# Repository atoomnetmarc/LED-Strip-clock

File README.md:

# Status

This project is in the idea stage.

Next step would be to test if the new schematic could work before ordering the first PCB.

# Why?

I made a huge LED clock with pieces of LED strip in 2013 using an [ATmega328 and DS3231 RTC](ATmega328%20version/). It has been running great and keeping time just fine. Lets break it by upgrading it.

This project will upgrade the ~~spagetti~~ old circuit to an internet connected LED strip clock neatly on a PCB. The brains will be a Wemos D1 mini and will use NTP to synchronize the time.

# Schematic

The [circuit](Kicad/LED%20Strip%20clock.pdf) recycles the same TPIC6B595 power shift registers and changes the ATmega328 for a ESP8266 and the DS3231 for a DS3231MZ. A 74HCT244 buffer translates between the 3.3V outputs of the ESP8266 and the 5V inputs of the shift register. The original circuit has a rotary encoder to set the light intensity and the current time. The new circuit will only use the rotary encoder to set the light intensity.

Render:

Real:

My [Kicad library](https://github.com/atoomnetmarc/ATOOMNETKICAD) is used in this project.

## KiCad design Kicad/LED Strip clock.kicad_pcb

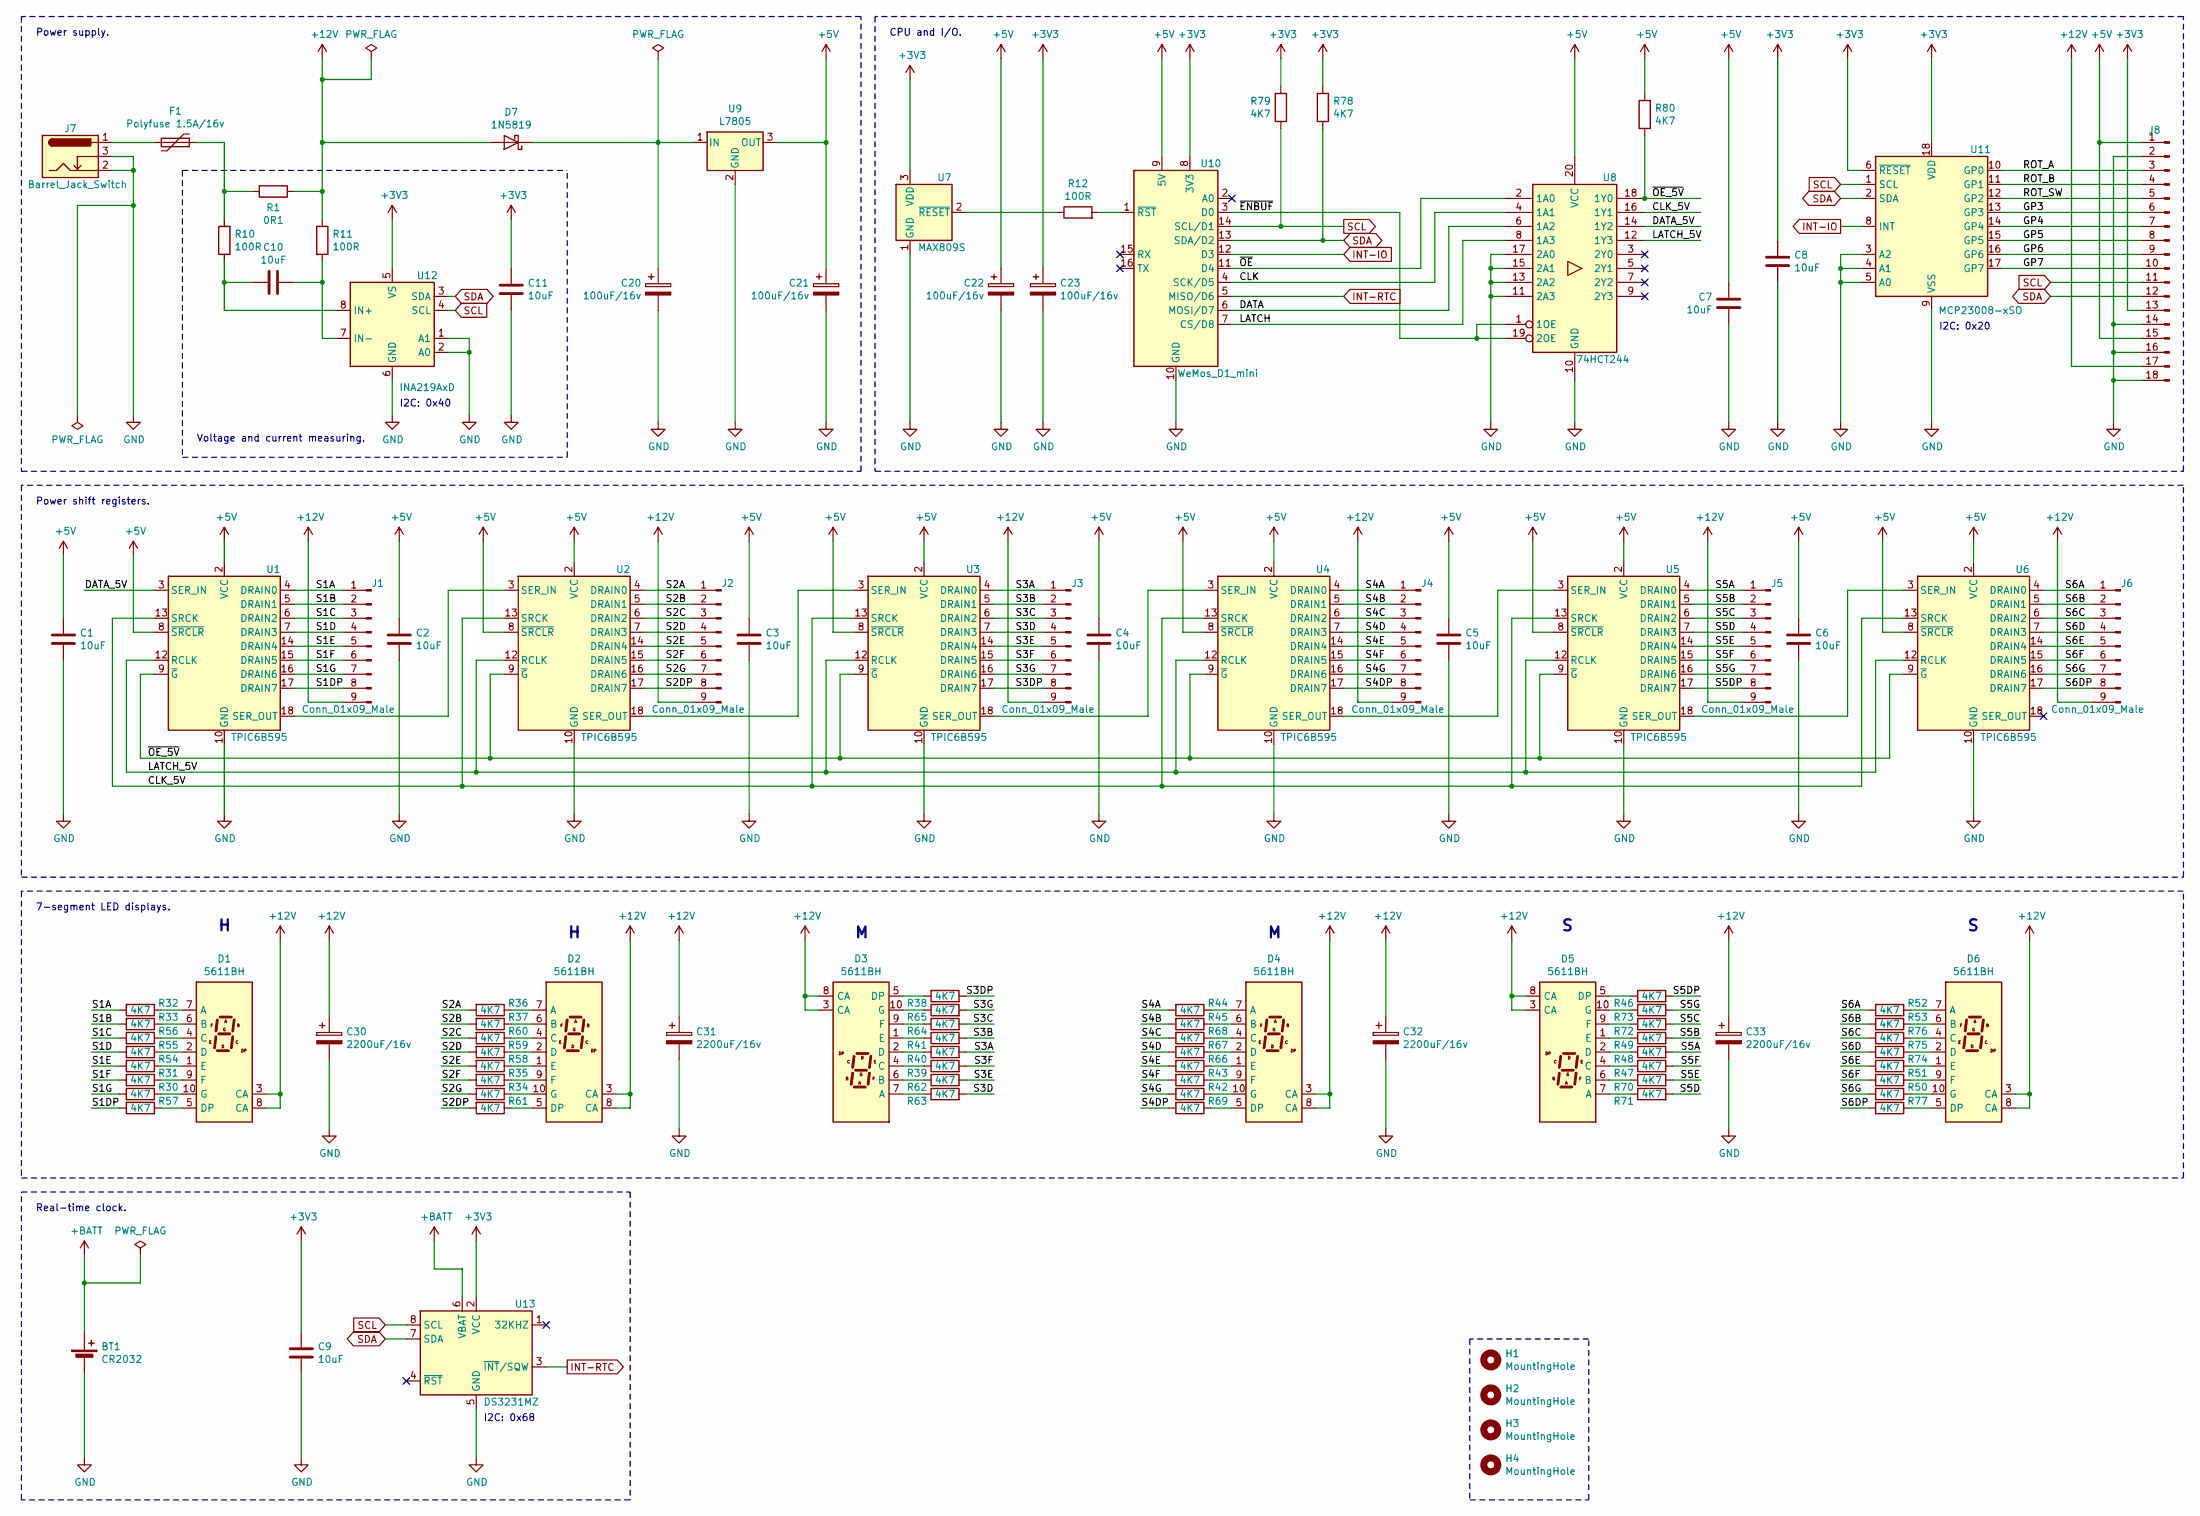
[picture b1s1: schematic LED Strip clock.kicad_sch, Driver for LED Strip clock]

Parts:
BT1: CR2032; BatteryHolder-cr2032
C1, C2, C3, C4, C5, C6, C7, C8, C9, C10, C11: 10uF; C_0805_2012Metric_Pad1.18x1.45mm_HandSolder
C20, C21, C22, C23: 100uF/16v; CP_Radial_D5.0mm_P2.00mm
C30, C31, C32, C33: 2200uF/16v; CP_Radial_D10.0mm_P5.00mm
D1, D2, D3, D4, D5, D6: 5611BH
D7: 1N5819; D_DO-41_SOD81_P10.16mm_Horizontal
F1: Polyfuse 1.5A/16v; Fuse_Bourns_MF-RG1000
H1, H2, H3, H4: MountingHole; MountingHole_3.2mm_M3
J1, J2, J3, J4, J5, J6: Conn_01x09_Male; PinHeader_1x09_P2.54mm_Vertical
J7: Barrel_Jack_Switch; BarrelJack_Horizontal
J8: Conn_01x18_Male; PinHeader_1x18_P2.54mm_Vertical
R1: 0R1; R_2512_6332Metric_Pad1.52x3.35mm_HandSolder
R10, R11, R12: 100R; R_0805_2012Metric_Pad1.20x1.40mm_HandSolder
R30, R31, R32, R33, R34, R35, R36, R37, R38, R39, R40, R41, R42, R43, R44, R45, R46, R47, R48, R49, R50, R51, R52, R53, R54, R55, R56, R57, R58, R59, R60, R61, R62, R63, R64, R65, R66, R67, R68, R69, R70, R71, R72, R73, R74, R75, R76, R77, R78, R79, R80: 4K7; R_0805_2012Metric_Pad1.20x1.40mm_HandSolder
U1, U2, U3, U4, U5, U6: TPIC6B595; DIP-20_W7.62mm_LongPads
U7: MAX809S; SOT-23
U8: 74HCT244; DIP-20_W7.62mm_LongPads
U9: L7805; TO-263-2
U10: WeMos_D1_mini; WEMOS_D1_mini_light
U11: MCP23008-xSO; SOIC-18W_7.5x11.6mm_P1.27mm
U12: INA219AxD; SOIC-8_3.9x4.9mm_P1.27mm
U13: DS3231MZ; SOIC-8_3.9x4.9mm_P1.27mm

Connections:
+3V3: C8.1, C9.1, C11.1, C23.1, J8.13, R78.2, R79.2, U7.3 (VDD), U10.8 (3V3), U11.6 (~RESET), U11.18 (VDD), U12.5 (VS), U13.2 (VCC)
+5V: C1.1, C2.1, C3.1, C4.1, C5.1, C6.1, C7.1, C21.1, C22.1, J8.1, J8.15, R80.2, U1.2 (VCC), U1.8 (~SRCLR), U2.2 (VCC), U2.8 (~SRCLR), U3.2 (VCC), U3.8 (~SRCLR), U4.2 (VCC), U4.8 (~SRCLR), U5.2 (VCC), U5.8 (~SRCLR), U6.2 (VCC), U6.8 (~SRCLR), U8.20 (VCC), U9.3 (OUT), U10.9 (5V)
+12V: C30.1, C31.1, C32.1, C33.1, D1.3 (CA), D1.8 (CA), D2.3 (CA), D2.8 (CA), D3.3 (CA), D3.8 (CA), D4.3 (CA), D4.8 (CA), D5.3 (CA), D5.8 (CA), D6.3 (CA), D6.8 (CA), D7.2 (A), J1.9, J2.9, J3.9, J4.9, J5.9, J6.9, J8.17, R1.1, R11.1
+BATT: BT1.1 (+), U13.6 (VBAT)
/CLK: U8.4 (1A1), U10.4 (SCK/D5)
/CLK_5V: U1.13 (SRCK), U2.13 (SRCK), U3.13 (SRCK), U4.13 (SRCK), U5.13 (SRCK), U6.13 (SRCK), U8.16 (1Y1)
/DATA: U8.6 (1A2), U10.6 (MOSI/D7)
/DATA_5V: U1.3 (SER_IN), U8.14 (1Y2)
/GP3: J8.6, U11.13 (GP3)
/GP4: J8.7, U11.14 (GP4)
/GP5: J8.8, U11.15 (GP5)
/GP6: J8.9, U11.16 (GP6)
/GP7: J8.10, U11.17 (GP7)
/LATCH: U8.8 (1A3), U10.7 (CS/D8)
/LATCH_5V: U1.12 (RCLK), U2.12 (RCLK), U3.12 (RCLK), U4.12 (RCLK), U5.12 (RCLK), U6.12 (RCLK), U8.12 (1Y3)
/ROT_A: J8.3, U11.10 (GP0)
/ROT_B: J8.4, U11.11 (GP1)
/ROT_SW: J8.5, U11.12 (GP2)
/S1A: J1.1, R32.2, U1.4 (DRAIN0)
/S1B: J1.2, R33.2, U1.5 (DRAIN1)
/S1C: J1.3, R56.2, U1.6 (DRAIN2)
/S1D: J1.4, R55.2, U1.7 (DRAIN3)
/S1DP: J1.8, R57.2, U1.17 (DRAIN7)
/S1E: J1.5, R54.2, U1.14 (DRAIN4)
/S1F: J1.6, R31.2, U1.15 (DRAIN5)
/S1G: J1.7, R30.2, U1.16 (DRAIN6)
/S2A: J2.1, R36.2, U2.4 (DRAIN0)
/S2B: J2.2, R37.2, U2.5 (DRAIN1)
/S2C: J2.3, R60.2, U2.6 (DRAIN2)
/S2D: J2.4, R59.2, U2.7 (DRAIN3)
/S2DP: J2.8, R61.2, U2.17 (DRAIN7)
/S2E: J2.5, R58.2, U2.14 (DRAIN4)
/S2F: J2.6, R35.2, U2.15 (DRAIN5)
/S2G: J2.7, R34.2, U2.16 (DRAIN6)
/S3A: J3.1, R40.2, U3.4 (DRAIN0)
/S3B: J3.2, R41.2, U3.5 (DRAIN1)
/S3C: J3.3, R64.2, U3.6 (DRAIN2)
/S3D: J3.4, R63.2, U3.7 (DRAIN3)
/S3DP: J3.8, R38.2, U3.17 (DRAIN7)
/S3E: J3.5, R62.2, U3.14 (DRAIN4)
/S3F: J3.6, R39.2, U3.15 (DRAIN5)
/S3G: J3.7, R65.2, U3.16 (DRAIN6)
/S4A: J4.1, R44.2, U4.4 (DRAIN0)
/S4B: J4.2, R45.2, U4.5 (DRAIN1)
/S4C: J4.3, R68.2, U4.6 (DRAIN2)
/S4D: J4.4, R67.2, U4.7 (DRAIN3)
/S4DP: J4.8, R69.2, U4.17 (DRAIN7)
/S4E: J4.5, R66.2, U4.14 (DRAIN4)
/S4F: J4.6, R43.2, U4.15 (DRAIN5)
/S4G: J4.7, R42.2, U4.16 (DRAIN6)
/S5A: J5.1, R48.2, U5.4 (DRAIN0)
/S5B: J5.2, R49.2, U5.5 (DRAIN1)
/S5C: J5.3, R72.2, U5.6 (DRAIN2)
/S5D: J5.4, R71.2, U5.7 (DRAIN3)
/S5DP: J5.8, R46.2, U5.17 (DRAIN7)
/S5E: J5.5, R70.2, U5.14 (DRAIN4)
/S5F: J5.6, R47.2, U5.15 (DRAIN5)
/S5G: J5.7, R73.2, U5.16 (DRAIN6)
/S6A: J6.1, R52.2, U6.4 (DRAIN0)
/S6B: J6.2, R53.2, U6.5 (DRAIN1)
/S6C: J6.3, R76.2, U6.6 (DRAIN2)
/S6D: J6.4, R75.2, U6.7 (DRAIN3)
/S6DP: J6.8, R77.2, U6.17 (DRAIN7)
/S6E: J6.5, R74.2, U6.14 (DRAIN4)
/S6F: J6.6, R51.2, U6.15 (DRAIN5)
/S6G: J6.7, R50.2, U6.16 (DRAIN6)
/~ENBUF: U8.1 (1OE), U8.19 (2OE), U10.3 (D0)
/~OE_5V: R80.1, U1.9 (~G), U2.9 (~G), U3.9 (~G), U4.9 (~G), U5.9 (~G), U6.9 (~G), U8.18 (1Y0)
/~OE: U8.2 (1A0), U10.11 (D4)
GND: BT1.2 (-), C1.2, C2.2, C3.2, C4.2, C5.2, C6.2, C7.2, C8.2, C9.2, C11.2, C20.2, C21.2, C22.2, C23.2, C30.2, C31.2, C32.2, C33.2, J7.2, J7.3, J8.2, J8.14, J8.16, J8.18, U1.1 (NC), U1.10 (GND), U1.11 (GND), U1.19 (GND), U1.20 (NC), U2.1 (NC), U2.10 (GND), U2.11 (GND), U2.19 (GND), U2.20 (NC), U3.1 (NC), U3.10 (GND), U3.11 (GND), U3.19 (GND), U3.20 (NC), U4.1 (NC), U4.10 (GND), U4.11 (GND), U4.19 (GND), U4.20 (NC), U5.1 (NC), U5.10 (GND), U5.11 (GND), U5.19 (GND), U5.20 (NC), U6.1 (NC), U6.10 (GND), U6.11 (GND), U6.19 (GND), U6.20 (NC), U7.1 (GND), U8.10 (GND), U8.11 (2A3), U8.13 (2A2), U8.15 (2A1), U8.17 (2A0), U9.2 (GND), U10.10 (GND), U11.3 (A2), U11.4 (A1), U11.5 (A0), U11.9 (VSS), U12.1 (A1), U12.2 (A0), U12.6 (GND), U13.5 (GND)
INT-IO: U10.12 (D3), U11.8 (INT)
INT-RTC: U10.5 (MISO/D6), U13.3 (~INT/SQW)
unnamed: C10.1, R10.1, U12.8 (IN+)
unnamed: C10.2, R11.2, U12.7 (IN-)
unnamed: C20.1, D7.1 (K), U9.1 (IN)
unnamed: D1.1 (E), R54.1
unnamed: D1.2 (D), R55.1
unnamed: D1.4 (C), R56.1
unnamed: D1.5 (DP), R57.1
unnamed: D1.6 (B), R33.1
unnamed: D1.7 (A), R32.1
unnamed: D1.9 (F), R31.1
unnamed: D1.10 (G), R30.1
unnamed: D2.1 (E), R58.1
unnamed: D2.2 (D), R59.1
unnamed: D2.4 (C), R60.1
unnamed: D2.5 (DP), R61.1
unnamed: D2.6 (B), R37.1
unnamed: D2.7 (A), R36.1
unnamed: D2.9 (F), R35.1
unnamed: D2.10 (G), R34.1
unnamed: D3.1 (E), R41.1
unnamed: D3.2 (D), R40.1
unnamed: D3.4 (C), R39.1
unnamed: D3.5 (DP), R38.1
unnamed: D3.6 (B), R62.1
unnamed: D3.7 (A), R63.1
unnamed: D3.9 (F), R64.1
unnamed: D3.10 (G), R65.1
unnamed: D4.1 (E), R66.1
unnamed: D4.2 (D), R67.1
unnamed: D4.4 (C), R68.1
unnamed: D4.5 (DP), R69.1
unnamed: D4.6 (B), R45.1
unnamed: D4.7 (A), R44.1
unnamed: D4.9 (F), R43.1
unnamed: D4.10 (G), R42.1
unnamed: D5.1 (E), R49.1
unnamed: D5.2 (D), R48.1
unnamed: D5.4 (C), R47.1
unnamed: D5.5 (DP), R46.1
unnamed: D5.6 (B), R70.1
unnamed: D5.7 (A), R71.1
unnamed: D5.9 (F), R72.1
unnamed: D5.10 (G), R73.1
unnamed: D6.1 (E), R74.1
unnamed: D6.2 (D), R75.1
unnamed: D6.4 (C), R76.1
unnamed: D6.5 (DP), R77.1
unnamed: D6.6 (B), R53.1
unnamed: D6.7 (A), R52.1
unnamed: D6.9 (F), R51.1
unnamed: D6.10 (G), R50.1
unnamed: F1.1, R1.2, R10.2
unnamed: F1.2, J7.1
unnamed: R12.1, U7.2 (~RESET)
unnamed: R12.2, U10.1 (~RST)
unnamed: U1.18 (SER_OUT), U2.3 (SER_IN)
unnamed: U2.18 (SER_OUT), U3.3 (SER_IN)
unnamed: U3.18 (SER_OUT), U4.3 (SER_IN)
unnamed: U4.18 (SER_OUT), U5.3 (SER_IN)
unnamed: U5.18 (SER_OUT), U6.3 (SER_IN)
SCL: J8.11, R79.1, U10.14 (SCL/D1), U11.1 (SCL), U12.4 (SCL), U13.8 (SCL)
SDA: J8.12, R78.1, U10.13 (SDA/D2), U11.2 (SDA), U12.3 (SDA), U13.7 (SDA)

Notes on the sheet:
Power supply.
Real-time clock.
Voltage and current measuring.
CPU and I/O.
I2C: 0x68
I2C: 0x40
Power shift registers.
7-segment LED displays.
I2C: 0x20

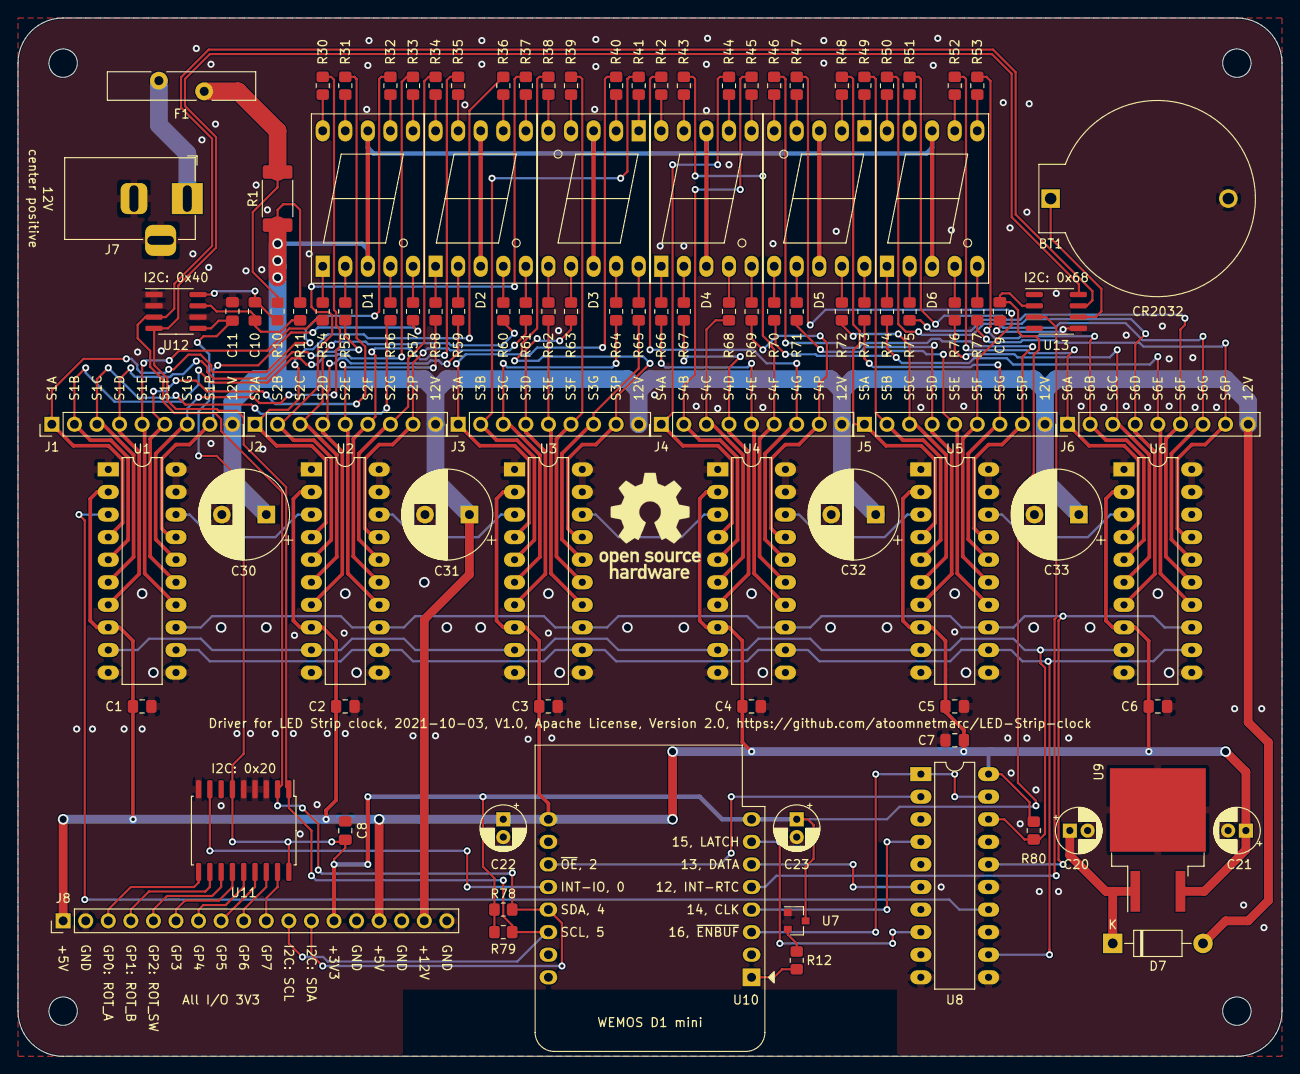
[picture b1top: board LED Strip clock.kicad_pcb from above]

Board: 2 copper layers, 142.2 x 116.8 mm, 108 parts (0 on the bottom side), 134 nets.

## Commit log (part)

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2021-08-06 Changed INA219AxDCN to INA219AxD.
2021-08-06 New render
2021-08-29 7-seg test.
2021-08-30 Fixed power-on flash of digits.
2021-08-30 Minor schematic tweaks.
2021-09-11 Change board layout. Add RTC. Add seconds LED display.
2021-09-21 Generate gerber and BOM.
2021-10-03 Change footprint of 7805 to D2PAK.
2021-10-03 Add output files.
2021-10-08 Add pcb holder.
2021-10-09 Add photo of real board.
2021-10-09 Start of firmware.
2021-11-13 Lower interval of NTP.
2026-01-23 Add CONTRIBUTING.md

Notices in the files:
Kicad/LED Strip clock.kicad_pcb:
Driver for LED Strip clock, 2021-10-03, V1.0, Apache License, Version 2.0, https://github.com/atoomnetmarc/LED-Strip-clock
README.md:
License: Apache 2.0
